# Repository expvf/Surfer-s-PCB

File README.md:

# Surfer-s-PCB

A blinky pad that has written on it one of my favorite quotes.

I didn't really know what to do with the design so I added a little comic book reference.

The LEDs are lined up in the shape of a sephiroth tree because I thought it would be cool

# Why I made this

I designed this project as a piece of tech-art. Rather than a standard grid, the LEDs are arranged in the shape of the **Sephiroth Tree (Tree of Life)** to create a striking visual effect when powered on. 

It’s meant to be framed or kept on a desk as a conversation piece.
#BOM

## Features

* **LED Layout:** 10-LED Sephirothic configuration.

## Bill of Materials (BOM)

| Name | Purpose | Qty | Total (USD) | Distributor | Link |
| :--- | :--- | :--- | :--- | :--- | :--- |
| **PCB** | Main board | 1 | $3.50 | [JLCPCB](https://jlcpcb.com) | [View] |

> **Note:** Prices may vary based on shipping and current manufacturing promos.

## Media

## How to Use
1. **Order:** Upload the Gerber files to a manufacturer like JLCPCB.
2. **Assemble:** Solder the LEDs and resistors to the designated pads.
3. **Display:** Power it up and enjoy the glow!

## License
This project is open-source. Feel free to use the design for your own personal projects.

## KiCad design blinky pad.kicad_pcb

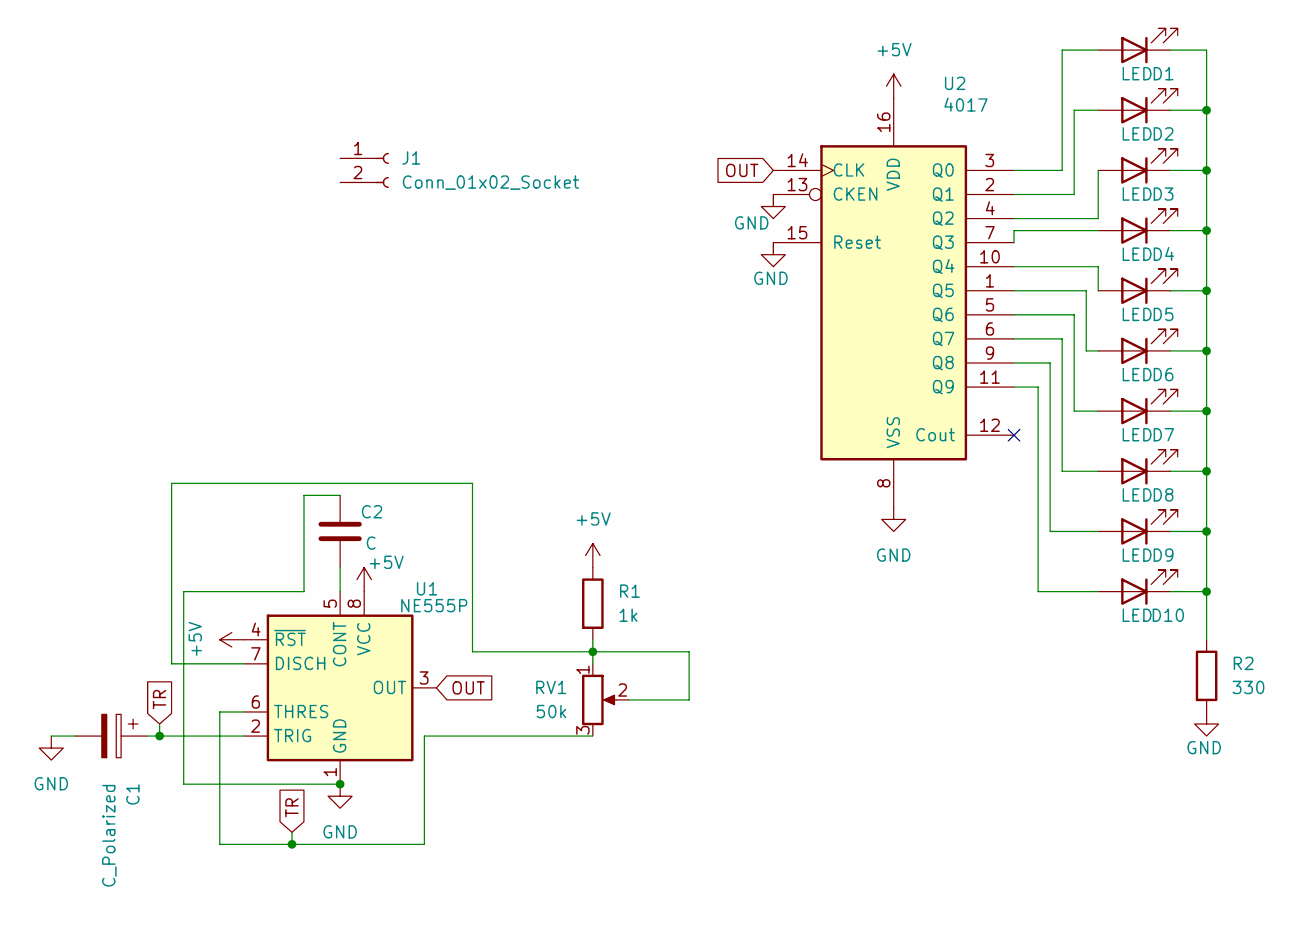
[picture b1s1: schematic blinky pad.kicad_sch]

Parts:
C1: C_Polarized; CP_Elec_3x5.3
C2: C; C_0402_1005Metric
D1, D2, D3, D4, D5, D6, D7, D8, D9, D10: LED; LED_0201_0603Metric
J1: Conn_01x02_Socket
R1: 1k; R_0201_0603Metric
R2: 330; R_0201_0603Metric
RV1: 50k; Potentiometer_ACP_CA6-H2,5_Horizontal
U1: NE555P; DIP-8_W7.62mm
U2: 4017; N16

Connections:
+5V: R1.1, U1.4 (~RST), U1.8 (VCC), U2.16 (VDD)
GND: C1.2, C2.1, R2.2, U1.1 (GND), U2.8 (VSS), U2.13 (CKEN), U2.15 (Reset)
unnamed: D1.2 (A), U2.3 (Q0)
unnamed: D1.1 (K), D2.1 (K), D3.1 (K), D4.1 (K), D5.1 (K), D6.1 (K), D7.1 (K), D8.1 (K), D9.1 (K), D10.1 (K), R2.1
unnamed: D2.2 (A), U2.2 (Q1)
unnamed: D3.2 (A), U2.4 (Q2)
unnamed: D4.2 (A), U2.7 (Q3)
unnamed: D5.2 (A), U2.10 (Q4)
unnamed: D6.2 (A), U2.1 (Q5)
unnamed: D7.2 (A), U2.5 (Q6)
unnamed: D8.2 (A), U2.6 (Q7)
unnamed: D9.2 (A), U2.9 (Q8)
unnamed: D10.2 (A), U2.11 (Q9)
unnamed: C2.2, U1.5 (CONT)
unnamed: R1.2, RV1.1, RV1.2, U1.7 (DISCH)
OUT: U1.3 (OUT), U2.14 (CLK)
TR: C1.1, RV1.3, U1.2 (TRIG), U1.6 (THRES)

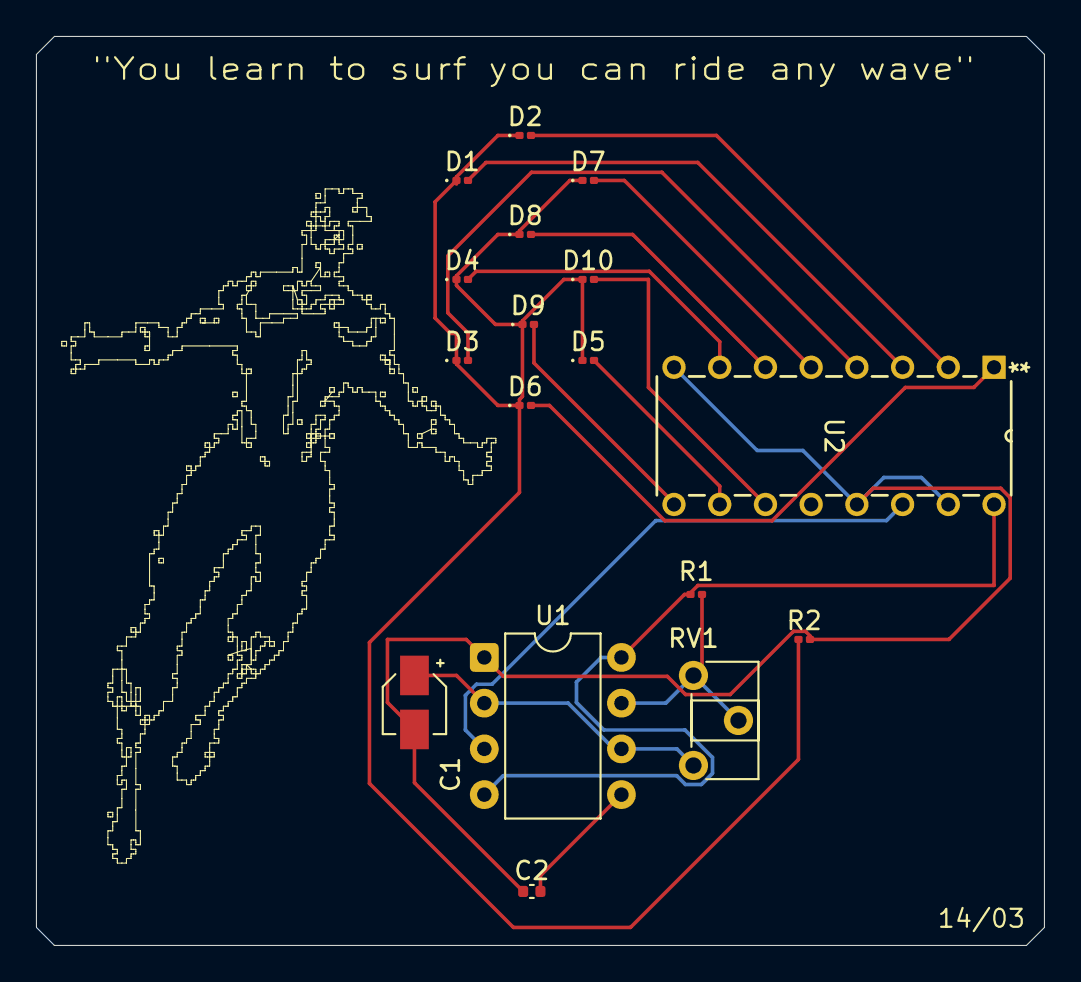
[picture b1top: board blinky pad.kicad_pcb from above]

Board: 2 copper layers, 56.0 x 50.5 mm, 17 parts (0 on the bottom side), 17 nets.
